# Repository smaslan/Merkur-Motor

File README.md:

# Stepper Motor Controller

This is simple project of one stepper motor controller designed for Czech toy 
[Merkur](https://www.merkurtoys.cz). It has manual speed and direction controlls and Bluetooth module for remote control via terminal commands or Android app. 
I don't expect this project as a whole would be useful to most people
but it may serve as a source for canibalization of some of its parts.

## Hardware

It was designed in a hurry from parts I had on hand so it's far from being optimal.
Core of the controller is 8-bit AVR [ATmega328PB](https://www.microchip.com/en-us/product/atmega328pb) (ATmega168PB would be enough). 
I used stepper motor [NEMA 17HS4023](https://www.google.com/search?q=NEMA+17+17HS4023) with bipolar coils.
I did not have proper stepper controller IC on hand, so I used cheap GaN fet driver ICs 
[1EDN7512B](https://www.infineon.com/cms/en/product/power/gate-driver-ics/1edn7512b/) with MOSFET half-bridge output.
These chips have undervoltage lockout (UVLO) circuit with threshold around 4.2V, which is kind of risky, because one of the bridge ICs will go to 
UVLO state before the other one, so there may be uninteruptable current via the winding when UVLO goes active. It won't be destructive, but it will discharge battery even faster, 
so UVLO is detected by AVR and it turns off power stage before it happens. Remote communication is made using cheap BT module
[JDY33-TTL](https://www.google.com/search?q=jdy33+ssp). Power stage, BT module and voltage sensing circuit can be switched off 
by power MOSFET to reduce idle power consumption to near zero (approx 2uA). Intended supply is from 4xAA NiMH accumulators, so there is 
5V voltage regulator for AVR. I used ultra-low quiscent current LDO TI [TPS709B50](https://www.ti.com/product/TPS709). 
Controlls are four buttons (Start, Stop, Left, Right) and encoder to setup speed.

The whole module was designed to fit in [plastic box](https://www.tme.eu/cz/details/km-276i_g/univerzalni-krabicky/maszczyk/). I wanted to make it smaller, but batteries are a bit large. Maybe in the next version. [PCB and diagram](./stepper_ctrl/) are available in Eagle format.

## AVR Firmware

Firmware for AVR is written in [Microchip Studio](https://www.microchip.com/en-us/tools-resources/develop/microchip-studio) using AVRGCC. 
Motor bridges are controlled by AVR PWM outputs which generate sine and cosine waves with modulation frequency of 78.125kHz, so it is kind of micro stepping driver. 
There is no current feedback from the stepper windings, so the current is controlled empirically by changing sine and consine amplitudes depending on motor speed. For the selected motor it should be approx 200 - 250mA with no load. Maximum speed is limited to 270rpm.
Reception of data via BT module is made in ISR to round buffer. Processing of the commands is done in main loop as well as controls state machine and other non-critical operations. Command interface uses simple [SCPI command](https://en.wikipedia.org/wiki/Standard_Commands_for_Programmable_Instruments) style commands set. Each command must be terminated by LF. Commands can be chained by semicolon. Answers are terminated by LF. Communication runs on BT module's default 9600bd. BT device name and its MAC address was left on default. List of supported commands:

```
 *IDN?                   - Return identification string.
 *OPC?                   - Wait for previous commands being processed, then returns 1.
 SYST:ERR?               - Return last error string.
 SYST:VMON?              - Return system voltage [V].
 SYST:TEMP?              - Return system temperature [degC].
 SYST:EESAVE             - Store current setup to EEPROM.
 SLEEP                   - Go to sleep mode immediately.
 SLEEP:TIMEOUT <timeout> - set sleep mode timeout [s].
 SLEEP:TIMEOUT?          - Get sleep timeout [s].
 SPEED <speed>           - Set motor speed in [rpm], signed value to set direction.
 SPEED?                  - Get current motor speed [rpm].
 SPEED:SET?              - Get last target (set) speed [rpm].
 SPEED:LIMIT <speed>     - Set speed limit [rpm].
 SPEED:LIMIT?            - Get speed limit [rpm].
 MOT:ACC <acc>           - Set motor acceleration constant [rpm/s].
 MOT:ACC?                - Get motor acceleration constant [rpm/s].
 START                   - Start motor to last set speed and direcion.
 STOP                    - Stop motor.
 DIR <direction>         - set motor direction (CW or CCW) 
                           and eventually start motor to previous speed.
```

Controller has implemented timeout timer, so when no controls are changed or SCPI command received, it will go to power down mode. It will respond to START button press to wakeup. It can be forced to power down mode by holding STOP button or by SCPI command SLEEP. Battery voltage is measured continuously. When it drops below preset threshold it will start blinking red and eventually turn off.

AVR fuse bits:
```
 Extended byte: CFD = 0, BODLEVEL[2..0] = 101 
 High byte: BOOTRST = 1, BOOTSZ[1..0] = 00, EESAVE = 0, WDTON = 1, SPIEN = 0, DWEN = 0, RSTDISBL = 1
 Low byte: CKSEL[3..0] = 1111, SUT[1..0] = 11, CKOUT = 1, CKDIV8 = 1
```

Firmware is available at [stepper_ctrl/fw_stepper_v1/](./stepper_ctrl/fw_stepper_v1).

## Android controll app "Merkur Motor"

Stepper controller can be controlled by terminal, but it's not exactly practical, so I decided to make an app for Android. This was my first atempt ever, so be warned it is not nice and optimal code but may be still used to cannibalize some parts. 
After some reading I decided to give a try to [Android Studio](https://developer.android.com/studio) and popular language [Kotlin](https://kotlinlang.org). That turned out to be good choice. Especially Kotlin is nice and simple language compared to e.g. C++. 
At first I tried to use some BT serial libraries, but I was not able to deal with collisions between some libraries so I tried to make BT communication using basic libraries. That was simpler than expected. Basically just list paired BT devices, select one, open BT socket and get in/out streams. Done. The worst part was dealing with permissions and trying to deal with loss of communication e.g. when the BT device goes offline. But in the end it kind of works at least from Android 11 to 14. Source is available at [MerkurControl/](./MerkurControl/).

## License
All parts of the project are distributed under [MIT license](./README.txt).

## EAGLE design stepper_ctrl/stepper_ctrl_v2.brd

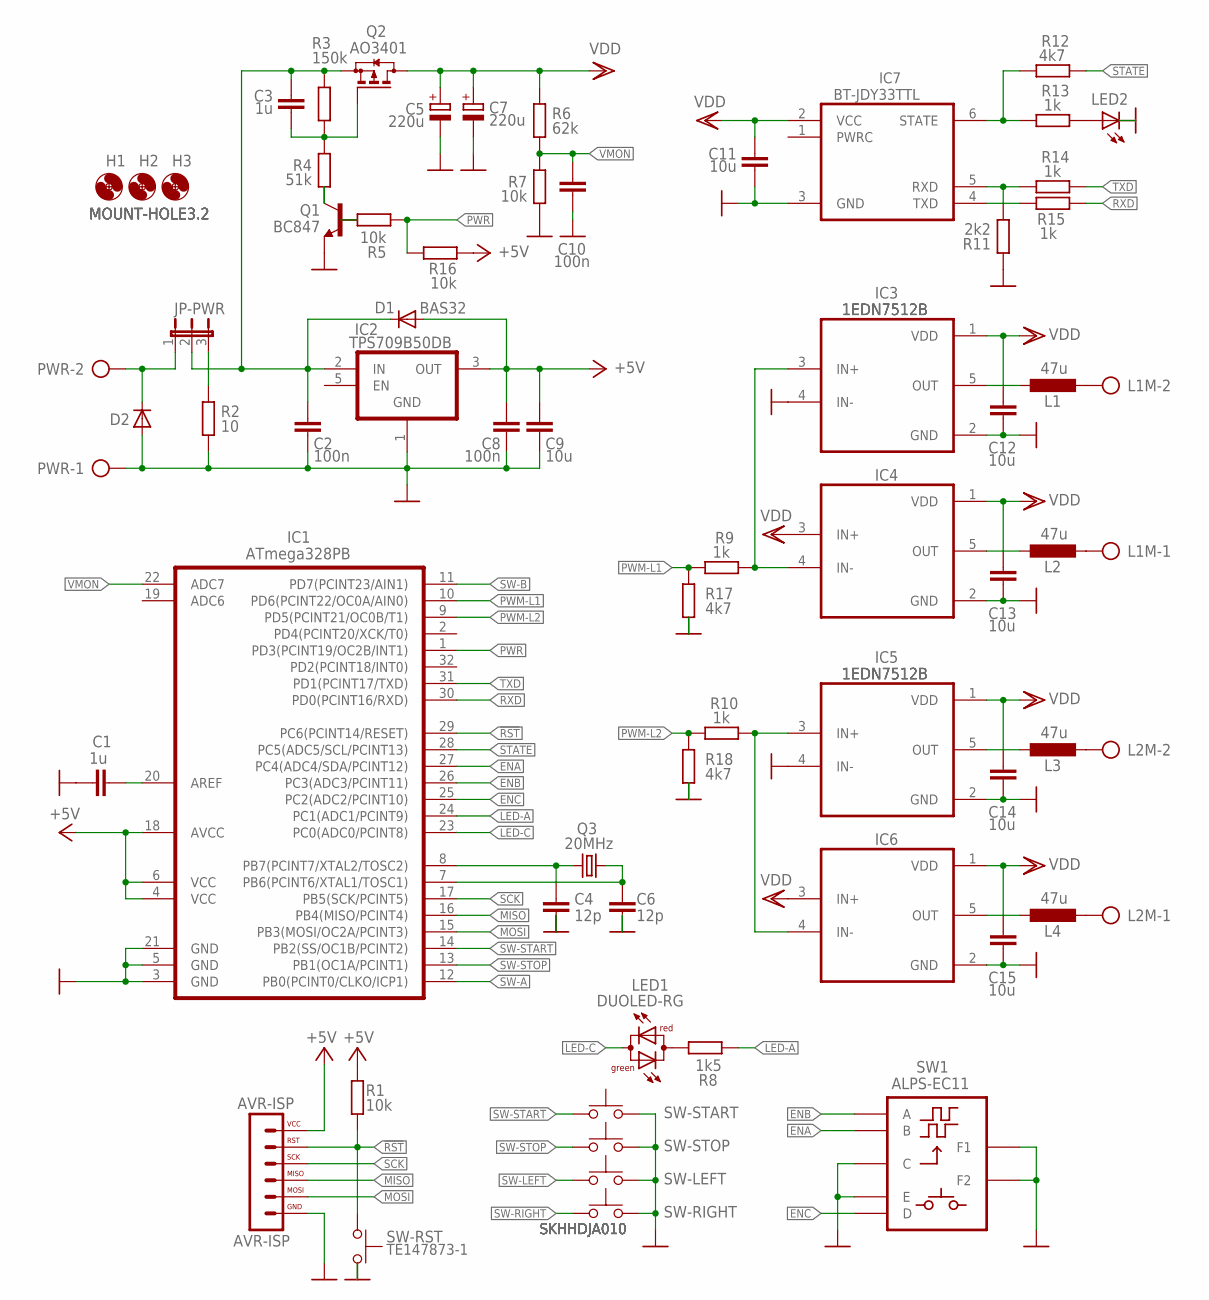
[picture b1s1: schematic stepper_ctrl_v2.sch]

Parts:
AVR-ISP: AVR-ISP; SIL6-NNRND
C1, C3: 1u; C0805K
C2, C8: 100n; C0805K
C4, C6: 12p; C0603K
C5, C7: 220u; E2,5-6
C9, C11, C12, C13, C14, C15: 10u; C0805K
C10: 100n; C0603K
D1: BAS32; SOD80C
D2: DIODE-SMB; SMB
H1, H2, H3: MOUNT-HOLE3.2; 3,2
IC1: ATmega328PB; TQFP32
IC2: TPS709B50DB; SOT23-5
IC3, IC4, IC5, IC6: 1EDN7512B; SOT23-5
IC7: BT-JDY33TTL; BT-JFY33TTL
JP-PWR: JP2EB; JP2YB
L1, L2, L3, L4: 47u; L4018
L1M, L2M: AK500/2
LED1: DUOLED-RG; LED3MM
LED2: LED3MM
PWR: AK500/2
Q1: BC847; SOT23
Q2: AO3401; SOT23
Q3: 20MHz; HC49U-V
R1, R5, R7, R16: 10k; R0603
R2: 10; R0805
R3: 150k; R0603
R4: 51k; R0603
R6: 62k; R0603
R8: 1k5; R0603
R9, R10, R13, R14, R15: 1k; R0603
R11: 2k2; R0603
R12, R17, R18: 4k7; R0603
SW1: ALPS-EC11; ALPS_EC11
SW-LEFT: SKHHDJA010; CUDL1
SW-RIGHT: SKHHDJA010; CUDL1
SW-RST: TE147873-1; TE-147873-1
SW-START: SKHHDJA010; CUDL1
SW-STOP: SKHHDJA010; CUDL1

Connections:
!RST: AVR-ISP.5, IC1.29 (PC6(PCINT14/RESET)), R1.2, SW-RST.P$2
+5V: AVR-ISP.6, C8.1, C9.1, D1.A, IC1.4 (VCC), IC1.6 (VCC), IC1.18 (AVCC), IC2.3 (OUT), R1.1, R16.2
ENA: IC1.27 (PC4(ADC4/SDA/PCINT12)), SW1.B
ENB: IC1.26 (PC3(ADC3/PCINT11)), SW1.A
ENC: IC1.25 (PC2(ADC2/PCINT10)), SW1.D
GND: AVR-ISP.1, C1.1, C2.2, C4.2, C5.-, C6.2, C7.-, C8.2, C9.2, C10.2, C11.2, C12.2, C13.2, C14.2, C15.2, D2.A, IC1.3 (GND), IC1.5 (GND), IC1.21 (GND), IC2.1 (GND), IC3.2 (GND), IC3.4 (IN-), IC4.2 (GND), IC5.2 (GND), IC5.4 (IN-), IC6.2 (GND), IC7.3 (GND), LED2.K (C), PWR.1, Q1.2 (E), R2.1, R7.1, R11.2, R17.2, R18.2, SW1.C, SW1.E, SW1.F1, SW1.F2, SW-LEFT.1, SW-LEFT.2, SW-RIGHT.1, SW-RIGHT.2, SW-RST.P$1, SW-START.1, SW-START.2, SW-STOP.1, SW-STOP.2
LED-A: IC1.24 (PC1(ADC1/PCINT9)), R8.1
LED-C: IC1.23 (PC0(ADC0/PCINT8)), LED1.K (C)
MISO: AVR-ISP.3, IC1.16 (PB4(MISO/PCINT4))
MOSI: AVR-ISP.2, IC1.15 (PB3(MOSI/OC2A/PCINT3))
unnamed: IC3.3 (IN+), IC4.4 (IN-), R9.1
unnamed: C1.2, IC1.20 (AREF)
unnamed: C2.1, C3.1, D1.C, IC2.2 (IN), JP-PWR.2, Q2.2 (S), R3.1
unnamed: D2.C, JP-PWR.1, PWR.2
unnamed: IC5.3 (IN+), IC6.4 (IN-), R10.1
unnamed: JP-PWR.3, R2.2
unnamed: LED2.A, R13.1
unnamed: IC7.6 (STATE), R12.2, R13.2
unnamed: IC7.5 (RXD), R11.1, R14.2
unnamed: IC7.4 (TXD), R15.2
unnamed: C4.1, IC1.8 (PB7(PCINT7/XTAL2/TOSC2)), Q3.1
unnamed: C6.1, IC1.7 (PB6(PCINT6/XTAL1/TOSC1)), Q3.2
unnamed: Q1.1 (B), R5.2
unnamed: LED1.A, R8.2
unnamed: IC3.5 (OUT), L1.2
unnamed: IC4.5 (OUT), L2.2
unnamed: IC5.5 (OUT), L3.2
unnamed: IC6.5 (OUT), L4.2
unnamed: L1.1, L1M.2
unnamed: L2M.2, L3.1
unnamed: L2M.1, L4.1
unnamed: L1M.1, L2.1
unnamed: C3.2, Q2.1 (G), R3.2, R4.2
unnamed: Q1.3 (C), R4.1
PWM-L1: IC1.10 (PD6(PCINT22/OC0A/AIN0)), R9.2, R17.1
PWM-L2: IC1.9 (PD5(PCINT21/OC0B/T1)), R10.2, R18.1
PWR: IC1.1 (PD3(PCINT19/OC2B/INT1)), R5.1, R16.1
RXD: IC1.30 (PD0(PCINT16/RXD)), R15.1
SCK: AVR-ISP.4, IC1.17 (PB5(SCK/PCINT5))
STATE: IC1.28 (PC5(ADC5/SCL/PCINT13)), R12.1
SW-A: IC1.12 (PB0(PCINT0/CLKO/ICP1))
SW-B: IC1.11 (PD7(PCINT23/AIN1))
SW-LEFT: SW-LEFT.3, SW-LEFT.4
SW-RIGHT: SW-RIGHT.3, SW-RIGHT.4
SW-START: IC1.14 (PB2(SS/OC1B/PCINT2)), SW-START.3, SW-START.4
SW-STOP: IC1.13 (PB1(OC1A/PCINT1)), SW-STOP.3, SW-STOP.4
TXD: IC1.31 (PD1(PCINT17/TXD)), R14.1
VDD: C5.+, C7.+, C11.1, C12.1, C13.1, C14.1, C15.1, IC3.1 (VDD), IC4.1 (VDD), IC4.3 (IN+), IC5.1 (VDD), IC6.1 (VDD), IC6.3 (IN+), IC7.2 (VCC), Q2.3 (D), R6.2
VMON: C10.1, IC1.22 (ADC7), R6.1, R7.2

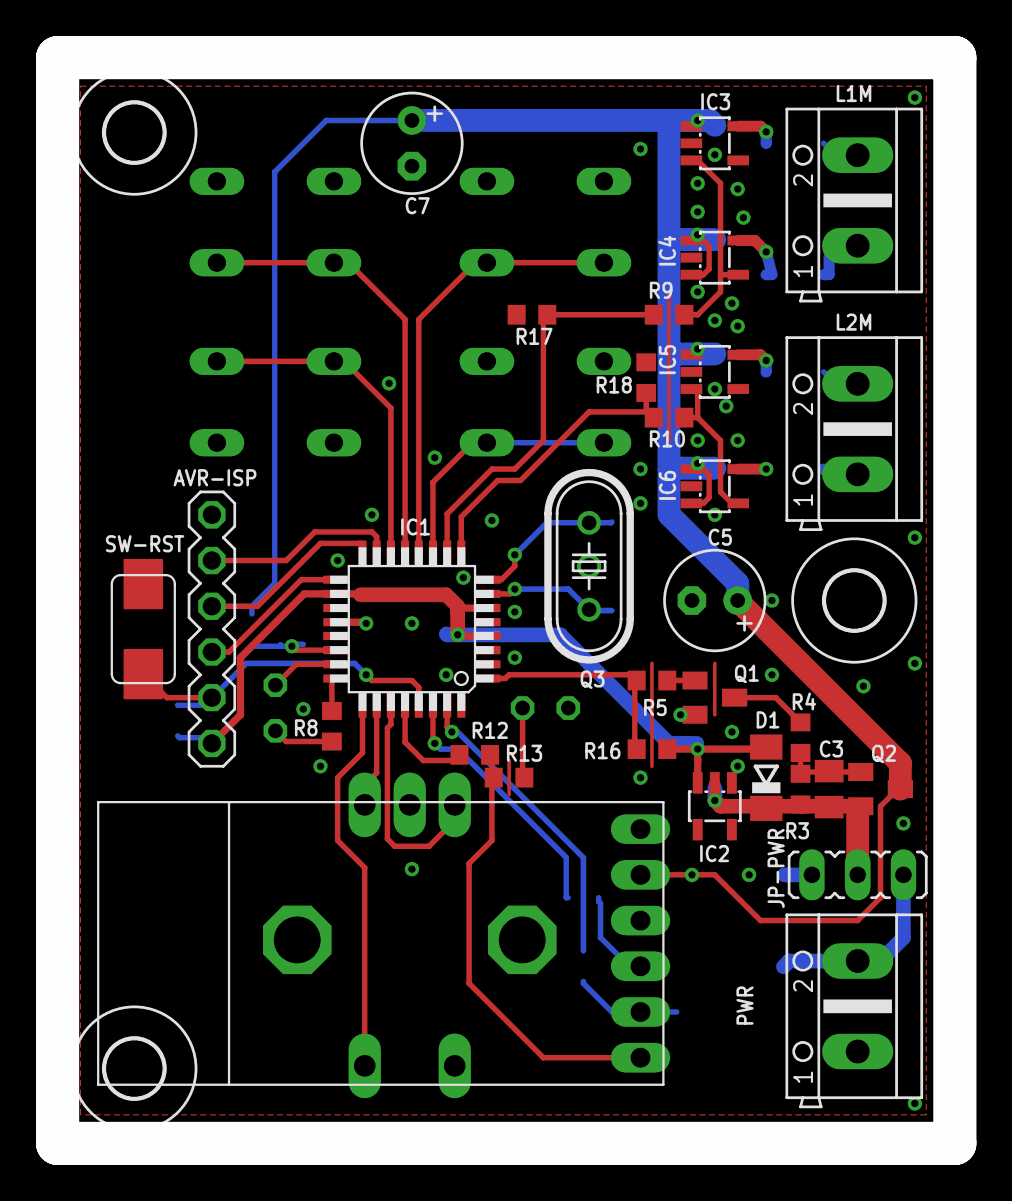
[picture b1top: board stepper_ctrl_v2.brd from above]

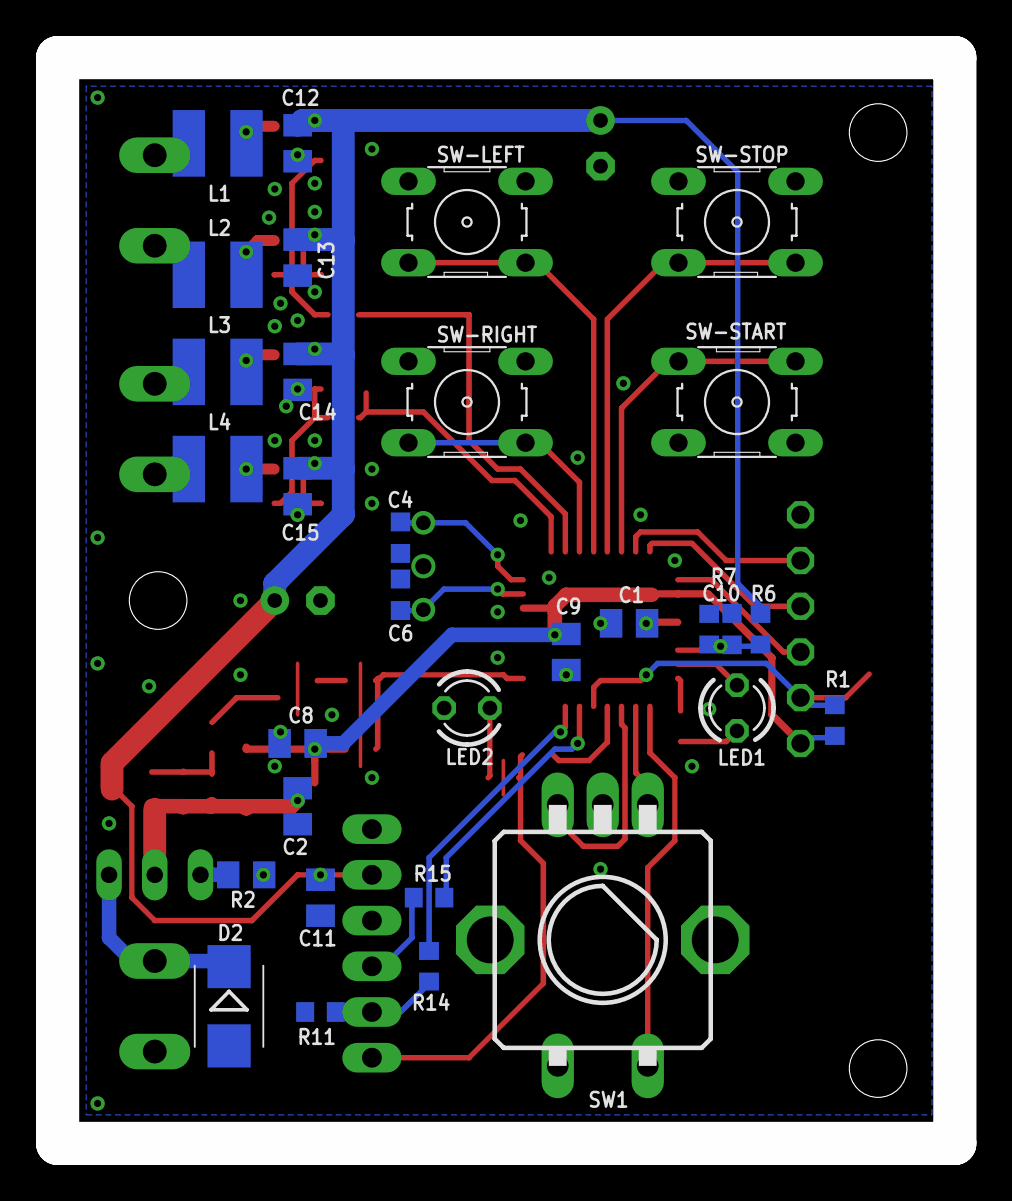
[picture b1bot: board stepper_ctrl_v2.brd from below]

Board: 2 copper layers, 49.8 x 60.3 mm, 65 parts (31 on the bottom side), 47 nets.

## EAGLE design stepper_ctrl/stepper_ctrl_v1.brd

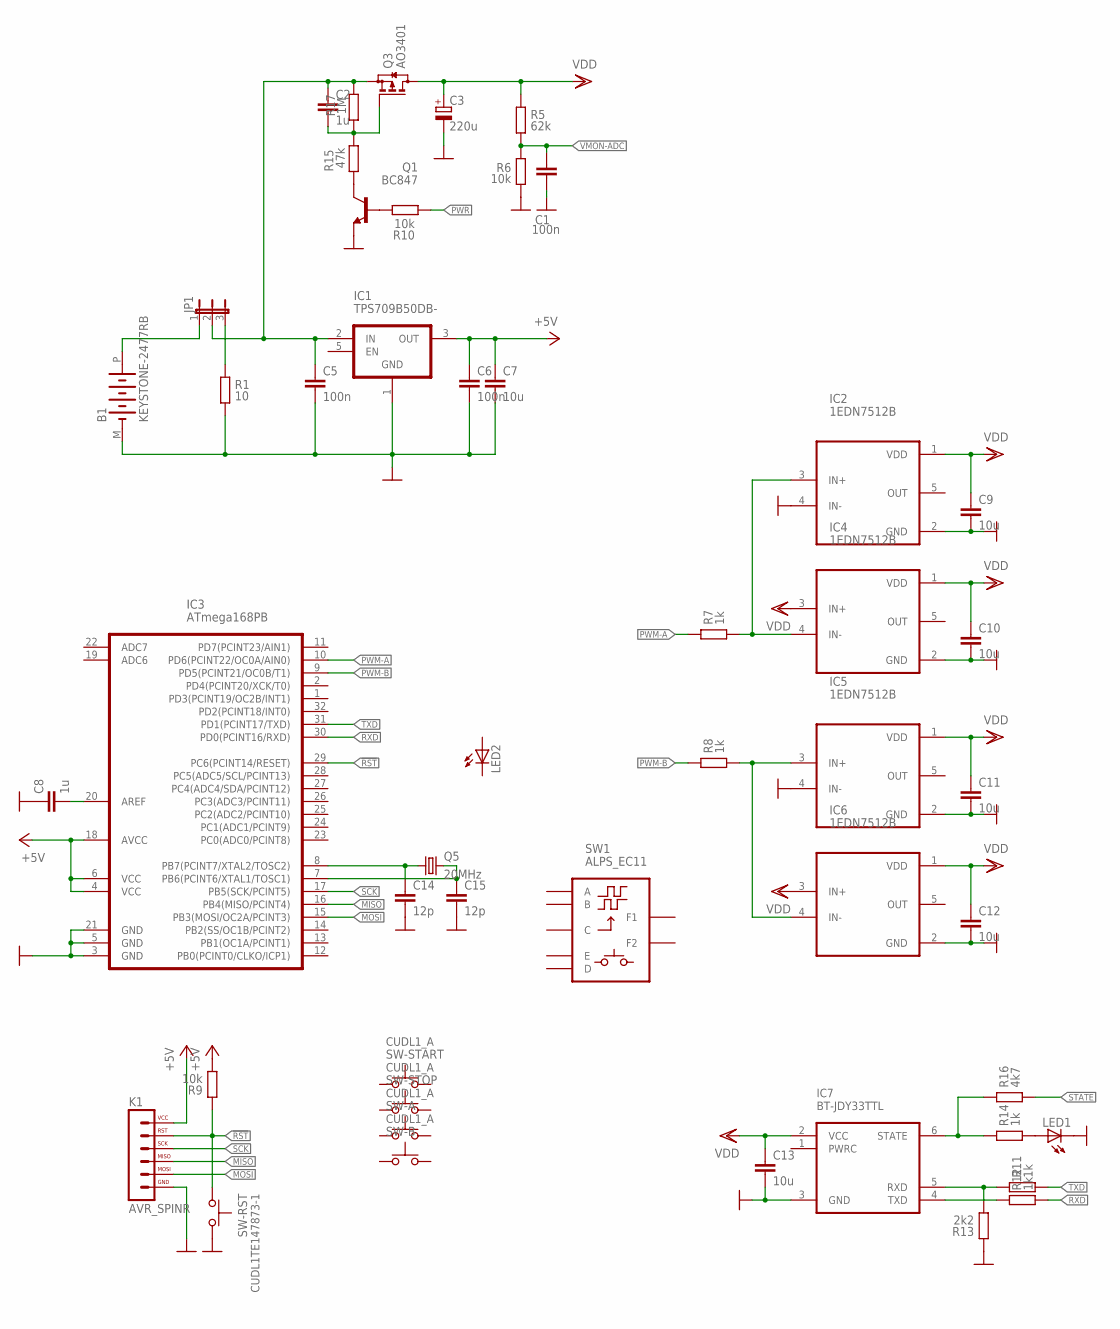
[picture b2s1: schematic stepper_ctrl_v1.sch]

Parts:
B1: KEYSTONE-2477RB
C1: 100n; C0603K
C2, C8: 1u; C0805K
C3: 220u; E2,5-7
C5, C6: 100n; C0805K
C7, C9, C10, C11, C12, C13: 10u; C0805K
C14, C15: 12p; C0603K
IC1: TPS709B50DB-; SOT23-5
IC2, IC4, IC5, IC6: 1EDN7512B; SOT23-5
IC3: ATmega168PB; TQFP32
IC7: BT-JDY33TTL; BT-JFY33TTL
JP1: JP2EB; JP2YB
K1: AVR_SPINR; SIL6-NNRND
LED1, LED2: LED3MM
Q1: BC847; SOT23
Q3: AO3401; SOT23
Q5: 20MHz; SMD32X25
R1: 10; R0805
R5: 62k; R0603
R6, R9, R10: 10k; R0603
R7, R8, R11, R12, R14: 1k; R0603
R13: 2k2; R0603
R15: 47k; R0603
R16: 4k7; R0603
R17: 1M; R0603
SW1: ALPS_EC11
SW-A: CUDL1_A; CUDL1
SW-B: CUDL1_A; CUDL1
SW-RST: CUDL1TE147873-1; TE-147873-1
SW-START: CUDL1_A; CUDL1
SW-STOP: CUDL1_A; CUDL1

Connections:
!RST: IC3.29 (PC6(PCINT14/RESET)), K1.5, R9.2, SW-RST.P$2
+5V: C6.1, C7.1, IC1.3 (OUT), IC3.4 (VCC), IC3.6 (VCC), IC3.18 (AVCC), K1.6, R9.1
GND: B1.M (-), C1.2, C3.-, C5.2, C6.2, C7.2, C8.1, C9.2, C10.2, C11.2, C12.2, C13.2, C14.2, C15.2, IC1.1 (GND), IC2.2 (GND), IC2.4 (IN-), IC3.3 (GND), IC3.5 (GND), IC3.21 (GND), IC4.2 (GND), IC5.2 (GND), IC5.4 (IN-), IC6.2 (GND), IC7.3 (GND), K1.1, LED1.K (C), Q1.2 (E), R1.1, R6.1, R13.2, SW-RST.P$1
MISO: IC3.16 (PB4(MISO/PCINT4)), K1.3
MOSI: IC3.15 (PB3(MOSI/OC2A/PCINT3)), K1.2
unnamed: IC2.3 (IN+), IC4.4 (IN-), R7.1
unnamed: C8.2, IC3.20 (AREF)
unnamed: C2.1, C5.1, IC1.2 (IN), JP1.2, Q3.2 (S), R17.1
unnamed: B1.P (+), JP1.1
unnamed: IC5.3 (IN+), IC6.4 (IN-), R8.1
unnamed: JP1.3, R1.2
unnamed: LED1.A, R14.1
unnamed: IC7.6 (STATE), R14.2, R16.2
unnamed: IC7.5 (RXD), R11.2, R13.1
unnamed: IC7.4 (TXD), R12.2
unnamed: C14.1, IC3.8 (PB7(PCINT7/XTAL2/TOSC2)), Q5.1
unnamed: C15.1, IC3.7 (PB6(PCINT6/XTAL1/TOSC1)), Q5.3 (2)
unnamed: Q1.1 (B), R10.2
unnamed: C2.2, Q3.1 (G), R15.2, R17.2
unnamed: Q1.3 (C), R15.1
PWM-A: IC3.10 (PD6(PCINT22/OC0A/AIN0)), R7.2
PWM-B: IC3.9 (PD5(PCINT21/OC0B/T1)), R8.2
PWR: R10.1
RXD: IC3.30 (PD0(PCINT16/RXD)), R12.1
SCK: IC3.17 (PB5(SCK/PCINT5)), K1.4
STATE: R16.1
TXD: IC3.31 (PD1(PCINT17/TXD)), R11.1
VDD: C3.+, C9.1, C10.1, C11.1, C12.1, C13.1, IC2.1 (VDD), IC4.1 (VDD), IC4.3 (IN+), IC5.1 (VDD), IC6.1 (VDD), IC6.3 (IN+), IC7.2 (VCC), Q3.3 (D), R5.2
VMON-ADC: C1.1, R5.1, R6.2

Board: 2 copper layers, 49 parts (36 on the bottom side), 27 nets, no tracks yet.

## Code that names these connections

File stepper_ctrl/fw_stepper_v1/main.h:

/*
 * Simple stepper motor controller. More details here:
 * https://github.com/smaslan/Merkur-Motor
 *
 * (c) 2024-2025, Stanislav Maslan, s.maslan@seznam.cz
 * V1.0, 2025-01-01
 *
 * The code and all its part are distributed under MIT license
 * https://opensource.org/licenses/MIT.
 */ 

#ifndef MAIN_H
#define MAIN_H

// general macros
#define sbi(port,pin) {(port)|=(1<<pin);}
#define cbi(port,pin) {(port)&=~(1<<pin);}
#define min(a,b) ((a<b)?(a):(b))
#define max(a,b) ((a>b)?(a):(b))
#define bcopy(dreg,dpin,srreg,srpin) if(bit_is_set((srreg),(srpin))){sbi(dreg,dpin);}else{cbi(dreg,dpin);}
#define bcopy_v(dreg,dpin,srreg,srpin) if((srreg)&(1<<srpin)){sbi(dreg,dpin);}else{cbi(dreg,dpin);}
#define low(x) ((x) & 0xFFu)
#define high(x) (((x)>>8) & 0xFFu)

// PWR control (active high)
#define PWR_port PORTD
#define PWR_ddr DDRD
#define PWR PD3

// control switches (active low)
#define SW_A_port PORTB
#define SW_A_ddr DDRB
#define SW_A_pin PINB
#define SW_A PB0
#define SW_B_port PORTD
#define SW_B_ddr DDRD
#define SW_B_pin PIND
#define SW_B PD7
#define SW_START_port PORTB
#define SW_START_ddr DDRB
#define SW_START_pin PINB
#define SW_START PB2
#define SW_STOP_port PORTB
#define SW_STOP_ddr DDRB
#define SW_STOP_pin PINB
#define SW_STOP PB1
#define SW_START_PCIE PCIE0
#define SW_START_PCMSK_REG PCMSK0
#define SW_START_PCMSK (1<<SW_START)
#define SW_START_ISR PCINT0_vect

// encoder (active low)
#define ENC_port PORTC
#define ENC_ddr DDRC
#define ENC_pin PINC
#define ENC_phy PC2
#define ENA_phy PC4
#define ENB_phy PC3
#define ENC 3
#define ENA 4
#define ENB 5
#define ENC_PCIE PCIE1
#define ENC_PCMSK_REG PCMSK1
#define ENC_PCMSK (1<<ENC_phy)
#define ENC_ISR PCINT1_vect

// BT state (active high)
#define BT_STATE_port PORTC
#define BT_STATE_ddr DDRC
#define BT_STATE_pin PINC
#define BT_STATE PC5

// serial port
#define UART_port PORTD
#define UART_ddr DDRD
#define UART_RXD PD0
#define UART_TXD PD1

// state LED (dual color)
#define LED_port PORTC
#define LED_ddr DDRC
#define LED_A PC1
#define LED_C PC0

// pulse outputs
#define PWM_port PORTD
#define PWM_ddr DDRD
#define PWM_L1 PD6
#define PWM_L2 PD5

// analogue inputs
#define ADC_VMON_MUX 0x07
#define ADC_TEMP_MUX 0x08
// ADC averaging
#define ADC_AVG 32 /* max 10bit*64 to scale to full 16bit */

// ADC data and stuff
typedef struct{
	volatile uint16_t a_vmon;
	volatile uint16_t a_temp;
	uint16_t vmon_alert;
}TADC;

// state LED modes
#define LED_IDLE 0
#define LED_RED 1
#define LED_GREEN 2
#define LED_RED_BLINK 3
#define LED_GREEN_BLINK 4
#define LED_RG_BLINK 5
#define LED_ORANGE 6

// system tick flag
#define SYS_10MS_TICK 0

// controls struct
typedef struct{
	volatile uint8_t downs;
	volatile uint8_t states;
	volatile uint8_t holds;
	volatile int8_t enc_delta;
	volatile uint8_t flags;
}TUI;

// encoder state changed (must not collide with button/encoder flags)
#define UI_ENC_CHANGE 6

// system setup to store to EEPROM
typedef struct{
	uint16_t sleep_timout;
	float mot_acc;
	float mot_speed_lim;
}TSetup;

// motor control
typedef struct{
	float speed;
	float speed_mem;
	float acc;
	float speed_act;
	float speed_lim;
	float speed_min;
	float speed_max;
	float amp_min;
	float amp_max;
	float amp_coef;
}TMotor;

// main system timer
#define SYS_TICK 0.001
#define SYS_TICK_DIV ((uint16_t)(F_CPU*SYS_TICK - 1))

// button hold off time [10ms]
#define BTN_HOLD_TIME 70

// battery undervolt alert voltage [V]
#define VMON_MIN_ALERT 4.2

// LED blink timeout for serial command [10ms]
#define LED_BLINK_TIMEOUT 25

// default sleep timeout [s]
#define SLEEP_TIMEOUT 60

// uvlo detection timeout [s]
#define UVLO_DET_TIMEOUT 5

// undervolt sleep timeout [s]
#define SLEEP_TIMEOUT_UVLO 3

// immediate sleep timeout [s]
#define SLEEP_TIMEOUT_NOW 0

// power stage voltage to allow sleep [V]
#define VMON_POWER_IDLE 2.0


#endif

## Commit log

2025-01-01 fix: readme.md
2025-01-05 add photos to README.md
2025-01-05 fix typo in README.md
